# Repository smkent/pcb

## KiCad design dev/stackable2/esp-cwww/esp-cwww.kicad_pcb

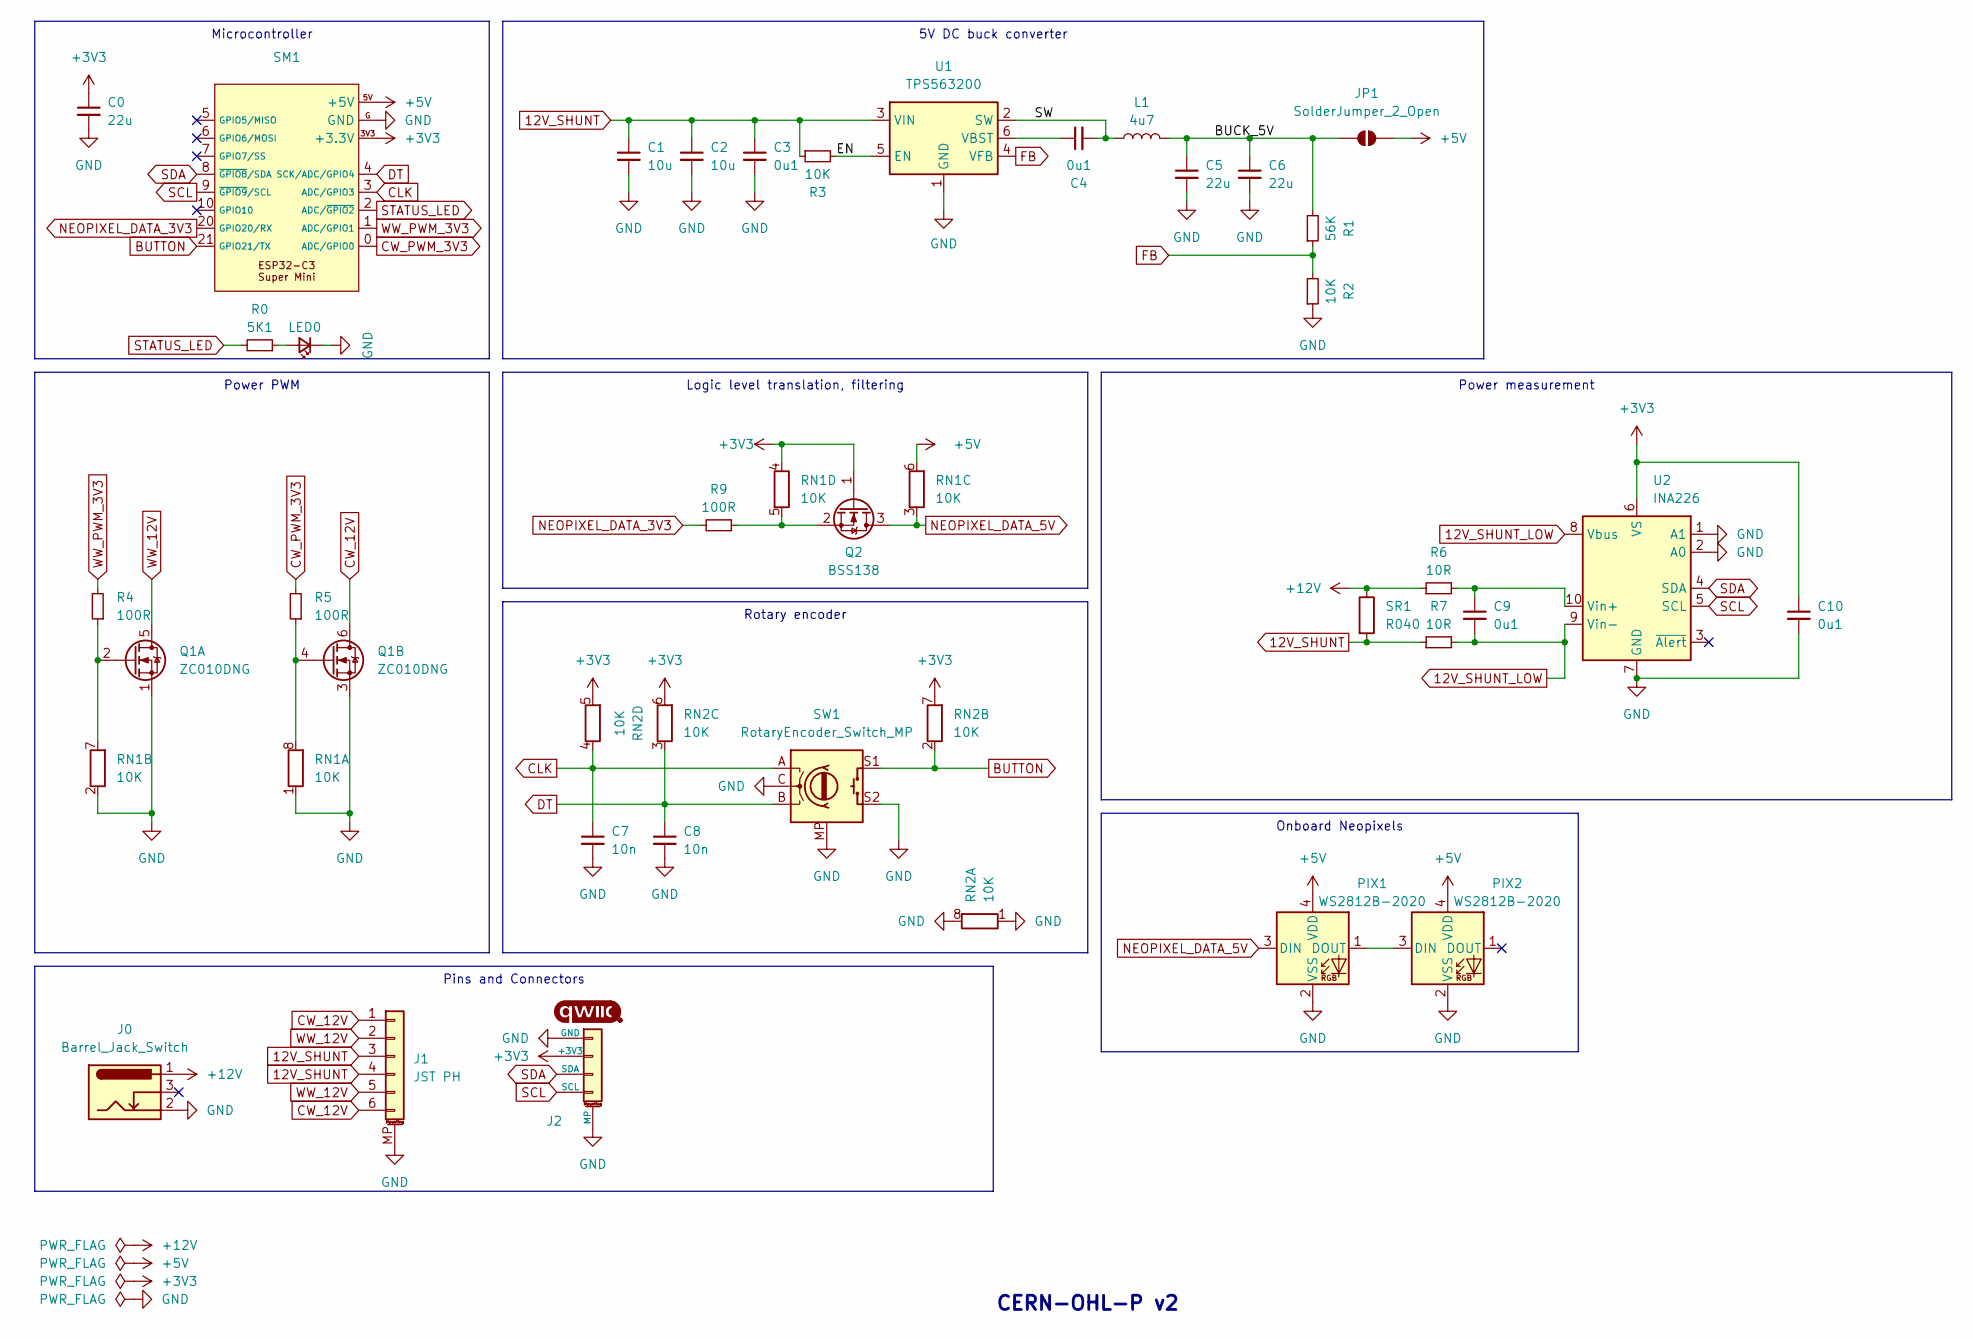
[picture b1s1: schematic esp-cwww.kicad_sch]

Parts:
C0, C5, C6: 22u; C_0603_1608Metric_Pad1.08x0.95mm_HandSolder
C1, C2: 10u; C_0603_1608Metric_Pad1.08x0.95mm_HandSolder
C3, C4: 0u1; C_0603_1608Metric_Pad1.08x0.95mm_HandSolder
C7, C8: 10n; C_0603_1608Metric_Pad1.08x0.95mm_HandSolder
C9, C10: 0u1; C_0402_1005Metric_simple; LCSC Part C1525
J0: Barrel_Jack_Switch; DC-IN_DC-050-2.0-BB_rev2
J1: JST PH; JST_PH_S6B-PH-SM4-TB_1x06-1MP_P2.00mm_Horizontal
J2: Qwiic; Qwiic-SMD-horizontal-logo
JP1: SolderJumper_2_Open; SolderJumper-2_P1.3mm_Open_TrianglePad1.0x1.5mm
L1: 4u7; IND-SMD_L2.5-W2.0_MHCHL2520
LED0: LED_Small; LED_0603_1608Metric_Pad1.05x0.95mm_HandSolder_simple
PIX1, PIX2: WS2812B-2020; LED-SK6812SIDE-A-4x1.6mm
Q1: ZC010DNG; PDFN-8_L3.2-W3.1-P0.65-LS3.4-BL-EP2; LCSC Part C36499170
Q2: BSS138; SOT-23_simple
R0: 5K1; R_0603_1608Metric_Pad0.98x0.95mm_HandSolder
R1: 56K; R_0603_1608Metric_Pad0.98x0.95mm_HandSolder
R2, R3: 10K; R_0603_1608Metric_Pad0.98x0.95mm_HandSolder
R4, R5, R9: 100R; R_0603_1608Metric_Pad0.98x0.95mm_HandSolder
R6: 10R; R_0402_1005Metric
R7: 10R; R_0402_1005Metric; LCSC Part C25077
RN1, RN2: 10K; R_Array_Convex_4x0603
SM1: ESP32-C3-Super-Mini-Castellated-SMD-only
SR1: R040; R_2512_6332Metric_Pad1.40x3.35mm_HandSolder; LCSC Part C2985725
SW1: RotaryEncoder_Switch_MP; RotaryEncoder_Alps_EC11-Switch_Combo_H20mm
U1: TPS563200; SOT-23-6_Handsoldering_simple
U2: INA226; VSSOP-10_3x3mm_P0.5mm

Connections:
12V_SHUNT: C1.1, C2.1, C3.1, J1.3, J1.4, R3.1, R7.1, SR1.2, U1.3 (VIN)
12V_SHUNT_LOW: C9.2, R7.2, U2.8 (Vbus), U2.9 (Vin-)
+3V3: C0.1, C10.1, J2.2 (+3V3), Q2.1 (G), RN1.4 (R4.1), RN2.5 (R4.2), RN2.6 (R3.2), RN2.7 (R2.2), SM1.3V3 (+3.3V), U2.6 (VS)
+5V: JP1.2 (B), PIX1.4 (VDD), PIX2.4 (VDD), RN1.6 (R3.2), SM1.5V (+5V)
+12V: J0.1, R6.1, SR1.1
/BUCK_5V: C5.1, C6.1, JP1.1 (A), L1.2, R1.2
/EN: R3.2, U1.5 (EN)
/SW: C4.2, L1.1, U1.2 (SW)
BUTTON: RN2.2 (R2.1), SM1.21 (GPIO21/TX), SW1.S1
CLK: C7.1, RN2.4 (R4.1), SM1.3 (ADC/GPIO3), SW1.A
CW_12V: J1.1, J1.6, Q1.6 (D)
CW_PWM_3V3: R5.2, SM1.0 (ADC/GPIO0)
DT: C8.1, RN2.3 (R3.1), SM1.4 (SCK/ADC/GPIO4), SW1.B
FB: R1.1, R2.2, U1.4 (VFB)
GND: C0.2, C1.2, C2.2, C3.2, C5.2, C6.2, C7.2, C8.2, C10.2, J0.2, J1.MP (MountPin), J2.1 (GND), J2.MP, LED0.1 (K), PIX1.2 (VSS), PIX2.2 (VSS), Q1.1 (S), Q1.3 (S), R2.1, RN1.1 (R1.1), RN1.2 (R2.1), RN2.1 (R1.1), RN2.8 (R1.2), SM1.G (GND), SW1.C, SW1.MP, SW1.S2, U1.1 (GND), U2.1 (A1), U2.2 (A0), U2.7 (GND)
NEOPIXEL_DATA_3V3: R9.2, SM1.20 (GPIO20/RX)
NEOPIXEL_DATA_5V: PIX1.3 (DIN), Q2.3 (D), RN1.3 (R3.1)
unnamed: LED0.2 (A), R0.1
unnamed: PIX1.1 (DOUT), PIX2.3 (DIN)
unnamed: Q1.2 (G), R4.1, RN1.7 (R2.2)
unnamed: Q1.4 (G), R5.1, RN1.8 (R1.2)
unnamed: Q2.2 (S), R9.1, RN1.5 (R4.2)
unnamed: C4.1, U1.6 (VBST)
unnamed: C9.1, R6.2, U2.10 (Vin+)
SCL: J2.4 (SCL), SM1.9 (~GPIO9/SCL), U2.5 (SCL)
SDA: J2.3 (SDA), SM1.8 (~GPIO8/SDA), U2.4 (SDA)
STATUS_LED: R0.2, SM1.2 (ADC/~GPIO2)
WW_12V: J1.2, J1.5, Q1.5 (D)
WW_PWM_3V3: R4.2, SM1.1 (ADC/GPIO1)

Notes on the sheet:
Rotary encoder
5V DC buck converter
Onboard Neopixels
Logic level translation, filtering
Power PWM
Power measurement
Pins and Connectors
Microcontroller
CERN-OHL-P v2

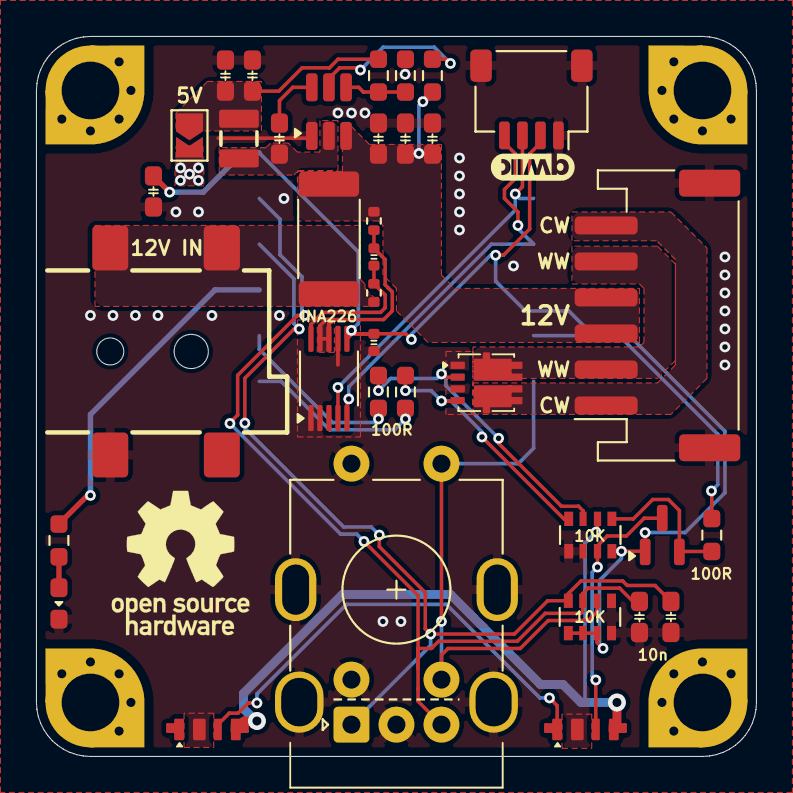
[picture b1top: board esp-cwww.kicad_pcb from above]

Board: 2 copper layers, 40.0 x 40.0 mm, 37 parts (1 on the bottom side), 29 nets.

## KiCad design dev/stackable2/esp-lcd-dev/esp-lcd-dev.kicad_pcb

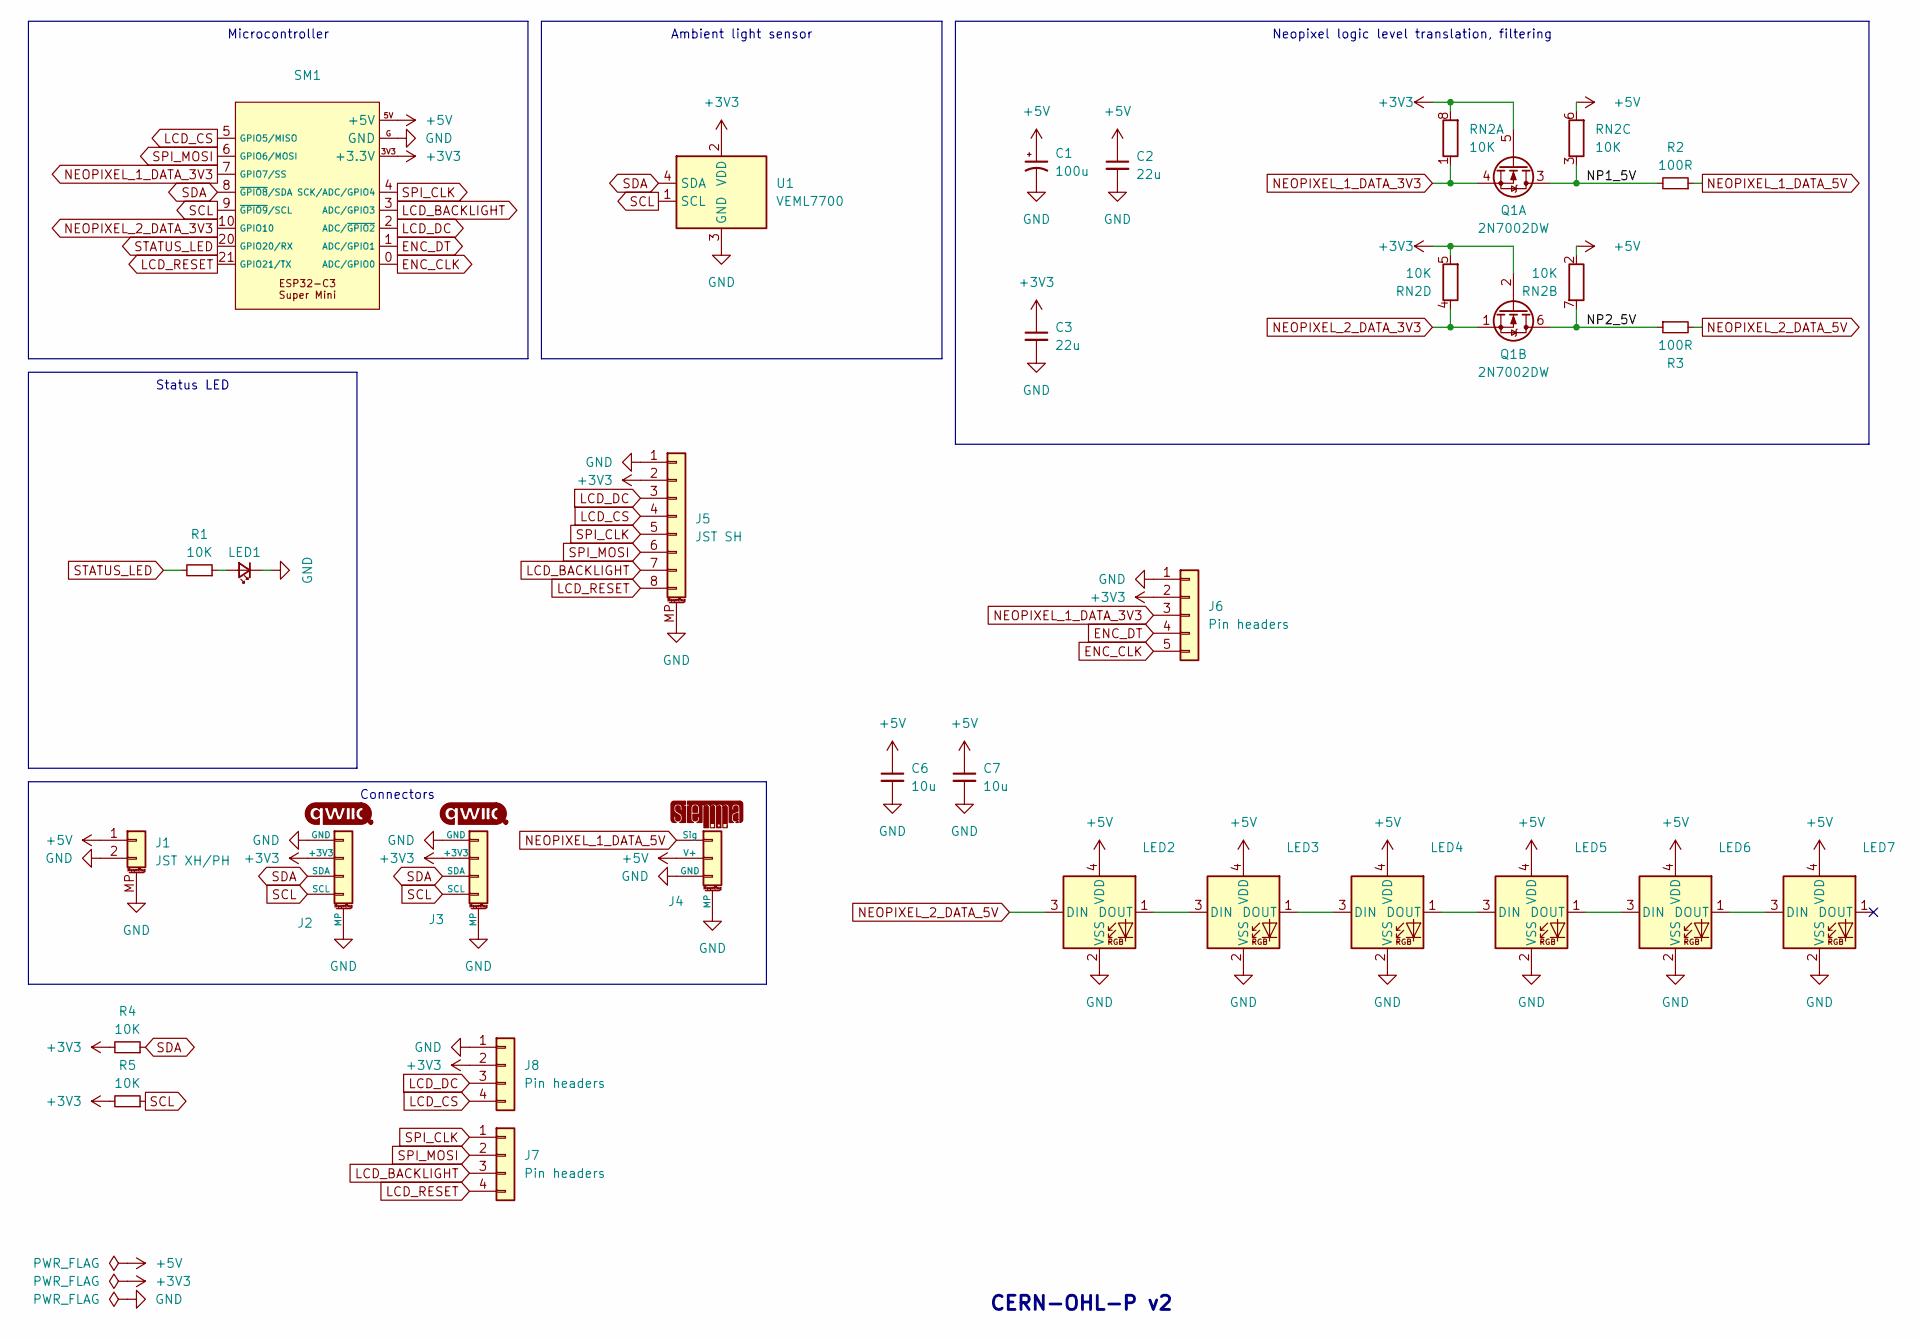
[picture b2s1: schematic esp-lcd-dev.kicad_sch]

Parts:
C1: 100u; CP_Elec_5x5.4
C2, C3: 22u; C_0603_1608Metric_Pad1.08x0.95mm_HandSolder
C6, C7: 10u; C_0603_1608Metric_Pad1.08x0.95mm_HandSolder
J1: JST XH/PH; Conn_Combo_JST-1x02-XH_PH-SMD-pad2gnd
J2, J3: Qwiic; Qwiic-SMD-horizontal-logo-bottom-pinout
J4: STEMMA-Signal; STEMMA-Signal-SMD-horizontal
J5: JST SH; JST_SH_SM08B-SRSS-TB_1x08-1MP_P1.00mm_Horizontal
J6: Pin headers; PinHeader_1x05_P2.54mm_Vertical_simple_pad1gnd
J7: Pin headers; PinSocket_1x04_P2.54mm_Vertical_SMD_Pin1Right
J8: Pin headers; PinSocket_1x04_P2.54mm_Vertical_SMD_Pin1Left
LED1: LED_Small; LED_0603_1608Metric_Pad1.05x0.95mm_HandSolder_simple
LED2, LED3, LED4, LED5, LED6, LED7: WS2812B-2020; LED-SMD_4P-L2.0-W2.0-BR-1
Q1: 2N7002DW; SOT-363_SC-70-6; LCSC Part C5190214
R1, R4, R5: 10K; R_0603_1608Metric_Pad0.98x0.95mm_HandSolder
R2, R3: 100R; R_0603_1608Metric_Pad0.98x0.95mm_HandSolder
RN2: 10K; R_Array_Convex_4x0603
SM1: ESP32-C3-Super-Mini-Castellated-SMD-only
U1: VEML7700; SENSORS-SMD_VEML7700-TR

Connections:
+3V3: C3.1, J2.2 (+3V3), J3.2 (+3V3), J5.2, J6.2, J8.2, Q1.2 (G), Q1.5 (G), R4.2, R5.2, RN2.5 (R4.2), RN2.8 (R1.2), SM1.3V3 (+3.3V), U1.2 (VDD)
+5V: C1.1, C2.1, C6.1, C7.1, J1.1, J4.2 (V+), LED2.4 (VDD), LED3.4 (VDD), LED4.4 (VDD), LED5.4 (VDD), LED6.4 (VDD), LED7.4 (VDD), RN2.2 (R2.1), RN2.6 (R3.2), SM1.5V (+5V)
/NP1_5V: Q1.3 (D), R2.2, RN2.3 (R3.1)
/NP2_5V: Q1.6 (D), R3.1, RN2.7 (R2.2)
ENC_CLK: J6.5, SM1.0 (ADC/GPIO0)
ENC_DT: J6.4, SM1.1 (ADC/GPIO1)
GND: C1.2, C2.2, C3.2, C6.2, C7.2, J1.2, J1.MP (MountPin), J2.1 (GND), J2.MP, J3.1 (GND), J3.MP, J4.3 (GND), J4.MP, J5.1, J5.MP (MountPin), J6.1, J8.1, LED1.1 (K), LED2.2 (VSS), LED3.2 (VSS), LED4.2 (VSS), LED5.2 (VSS), LED6.2 (VSS), LED7.2 (VSS), SM1.G (GND), U1.3 (GND)
LCD_BACKLIGHT: J5.7, J7.3, SM1.3 (ADC/GPIO3)
LCD_CS: J5.4, J8.4, SM1.5 (GPIO5/MISO)
LCD_DC: J5.3, J8.3, SM1.2 (ADC/~GPIO2)
LCD_RESET: J5.8, J7.4, SM1.21 (GPIO21/TX)
NEOPIXEL_1_DATA_3V3: J6.3, Q1.4 (S), RN2.1 (R1.1), SM1.7 (GPIO7/SS)
NEOPIXEL_1_DATA_5V: J4.1 (Sig), R2.1
NEOPIXEL_2_DATA_3V3: Q1.1 (S), RN2.4 (R4.1), SM1.10 (GPIO10)
NEOPIXEL_2_DATA_5V: LED2.3 (DIN), R3.2
unnamed: LED1.2 (A), R1.1
unnamed: LED2.1 (DOUT), LED3.3 (DIN)
unnamed: LED3.1 (DOUT), LED4.3 (DIN)
unnamed: LED4.1 (DOUT), LED5.3 (DIN)
unnamed: LED5.1 (DOUT), LED6.3 (DIN)
unnamed: LED6.1 (DOUT), LED7.3 (DIN)
SCL: J2.4 (SCL), J3.4 (SCL), R5.1, SM1.9 (~GPIO9/SCL), U1.1 (SCL)
SDA: J2.3 (SDA), J3.3 (SDA), R4.1, SM1.8 (~GPIO8/SDA), U1.4 (SDA)
SPI_CLK: J5.5, J7.1, SM1.4 (SCK/ADC/GPIO4)
SPI_MOSI: J5.6, J7.2, SM1.6 (GPIO6/MOSI)
STATUS_LED: R1.2, SM1.20 (GPIO20/RX)

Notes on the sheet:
Neopixel logic level translation, filtering
Connectors
Status LED
Ambient light sensor
Microcontroller
CERN-OHL-P v2

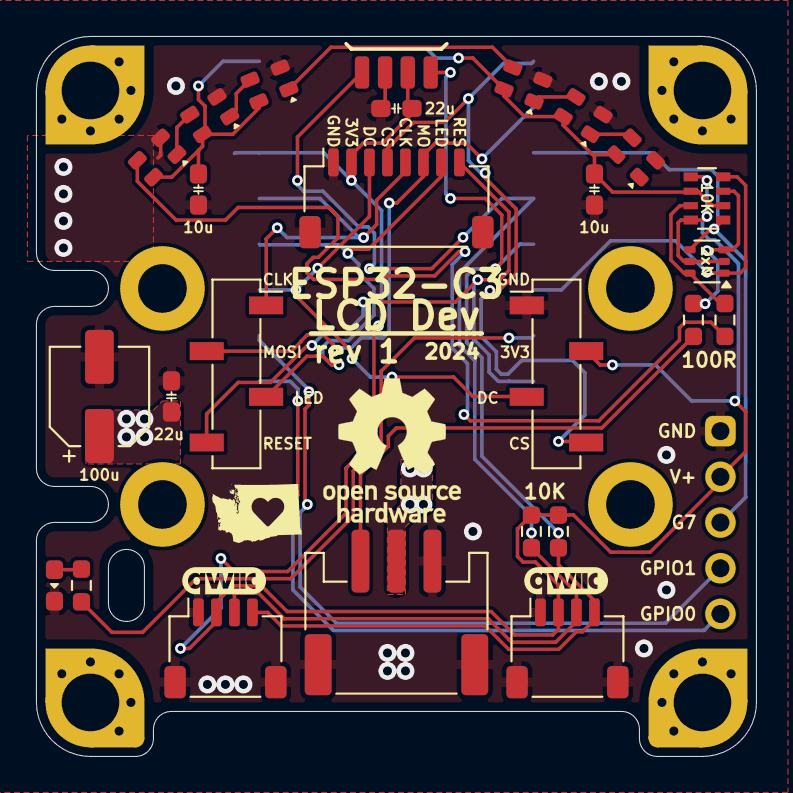
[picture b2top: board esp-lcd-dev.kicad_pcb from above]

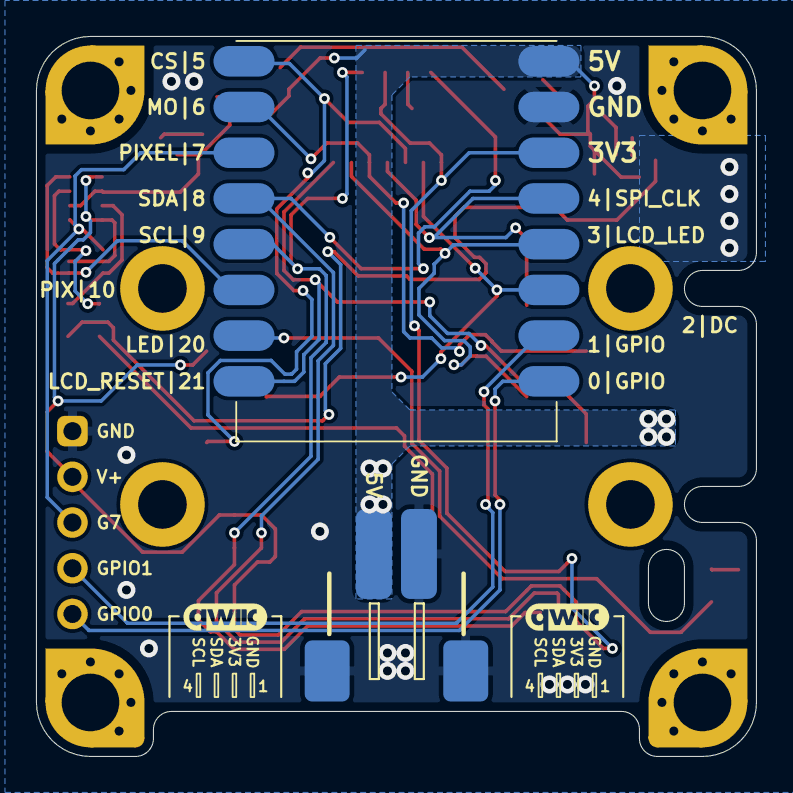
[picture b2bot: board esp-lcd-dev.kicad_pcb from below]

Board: 2 copper layers, 40.0 x 40.0 mm, 29 parts (3 on the bottom side), 26 nets.

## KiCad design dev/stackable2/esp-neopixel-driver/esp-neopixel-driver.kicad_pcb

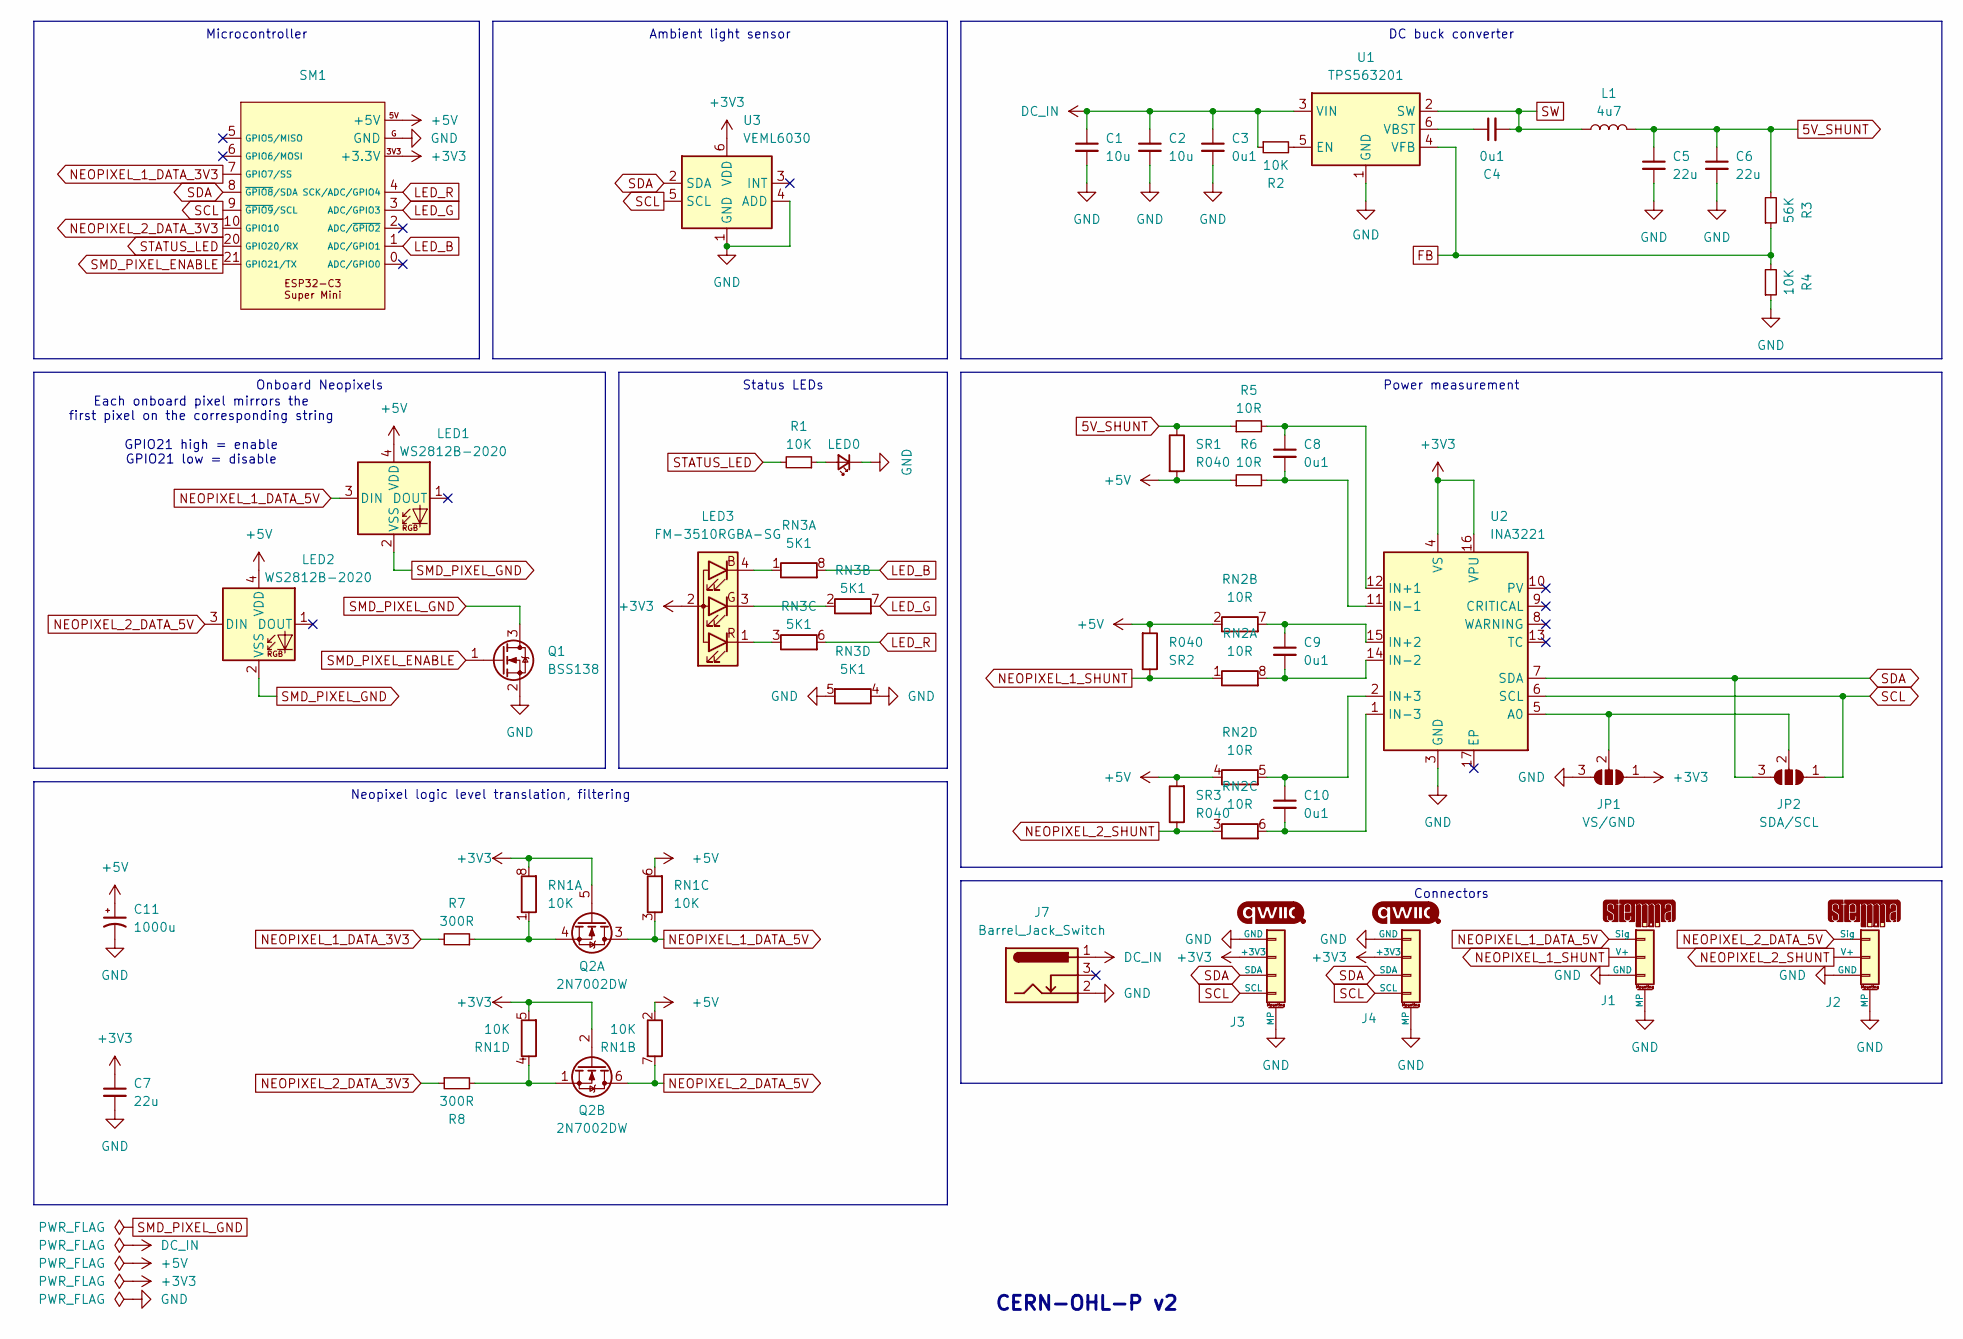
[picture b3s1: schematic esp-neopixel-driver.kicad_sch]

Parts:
C1, C2: 10u; C_0603_1608Metric_Pad1.08x0.95mm_HandSolder
C3, C4: 0u1; C_0603_1608Metric_Pad1.08x0.95mm_HandSolder
C5, C6: 22u; C_0805_2012Metric_Pad1.18x1.45mm_HandSolder
C7: 22u; C_0603_1608Metric_Pad1.08x0.95mm_HandSolder
C8, C9, C10: 0u1; C_0603_1608Metric_Pad1.08x0.95mm_HandSolder; LCSC Part C1525
C11: 1000u; CP_Elec_8x10
J1, J2: STEMMA-Signal; STEMMA-Signal-SMD-horizontal
J3, J4: Qwiic; Qwiic-SMD-horizontal-logo-bottom-pinout
J7: Barrel_Jack_Switch; DC-IN_DC-050-2.0-BB_rev2
JP1: VS/GND; SolderJumper-3_P1.0mm_Open_RoundedPad_simple
JP2: SDA/SCL; SolderJumper-3_P1.0mm_Open_RoundedPad_simple
L1: 4u7; IND-SMD_L2.5-W2.0_MHCHL2520; LCSC Part C22471106
LED0: LED_Small; LED-SMD_L1.7-W1.1-R-RD_BLUE
LED1, LED2: WS2812B-2020; LED-SMD_4P-L2.0-W2.0-BR-1
LED3: FM-3510RGBA-SG; LED-SMD_FM-3510RGBA-SG
Q1: BSS138; SOT-23_simple
Q2: 2N7002DW; SOT-363_SC-70-6; LCSC Part C5190214
R1, R2, R4: 10K; R_0603_1608Metric_Pad0.98x0.95mm_HandSolder
R3: 56K; R_0603_1608Metric_Pad0.98x0.95mm_HandSolder
R5: 10R; R_0603_1608Metric_Pad0.98x0.95mm_HandSolder_simple
R6: 10R; R_0603_1608Metric_Pad0.98x0.95mm_HandSolder_simple; LCSC Part C25077
R7, R8: 300R; R_0603_1608Metric_Pad0.98x0.95mm_HandSolder
RN1: 10K; R_Array_Convex_4x0603
RN2: 10R; R_Array_Convex_4x0603
RN3: 5K1; R_Array_Convex_4x0603
SM1: ESP32-C3-Super-Mini-Castellated-SMD-only
SR1, SR2, SR3: R040; R_2512_6332Metric_Pad1.40x3.35mm_HandSolder; LCSC Part C2985725
U1: TPS563201; SOT-23-6_Handsoldering_simple
U2: INA3221; Texas_RGV0016A_VQFN-16-1EP_4x4mm_P0.65mm_EP2.1x2.1mm_Therma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; LCSC Part C181255
U3: VEML6030; SENSORS-SMD_VEML6030

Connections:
5V_SHUNT: C5.1, C6.1, L1.2, R3.2, R5.1, SR1.1
+3V3: C7.1, J3.2 (+3V3), J4.2 (+3V3), JP1.1 (A), LED3.2 (A), Q2.2 (G), Q2.5 (G), RN1.5 (R4.2), RN1.8 (R1.2), SM1.3V3 (+3.3V), U2.4 (VS), U2.16 (VPU), U3.6 (VDD)
+5V: C11.1, LED1.4 (VDD), LED2.4 (VDD), R6.1, RN1.2 (R2.1), RN1.6 (R3.2), RN2.2 (R2.1), RN2.4 (R4.1), SM1.5V (+5V), SR1.2, SR2.2, SR3.2
DC_IN: C1.1, C2.1, C3.1, J7.1, R2.1, U1.3 (VIN)
FB: R3.1, R4.2, U1.4 (VFB)
GND: C1.2, C2.2, C3.2, C5.2, C6.2, C7.2, C11.2, J1.3 (GND), J1.MP, J2.3 (GND), J2.MP, J3.1 (GND), J3.MP, J4.1 (GND), J4.MP, J7.2, JP1.3 (B), LED0.1 (K), Q1.2 (S), R4.1, RN3.4 (R4.1), RN3.5 (R4.2), SM1.G (GND), U1.1 (GND), U2.3 (GND), U3.1 (GND), U3.4 (ADD)
LED_B: RN3.8 (R1.2), SM1.1 (ADC/GPIO1)
LED_G: RN3.7 (R2.2), SM1.3 (ADC/GPIO3)
LED_R: RN3.6 (R3.2), SM1.4 (SCK/ADC/GPIO4)
NEOPIXEL_1_DATA_3V3: R7.2, SM1.7 (GPIO7/SS)
NEOPIXEL_1_DATA_5V: J1.1 (Sig), LED1.3 (DIN), Q2.3 (D), RN1.3 (R3.1)
NEOPIXEL_1_SHUNT: J1.2 (V+), RN2.1 (R1.1), SR2.1
NEOPIXEL_2_DATA_3V3: R8.1, SM1.10 (GPIO10)
NEOPIXEL_2_DATA_5V: J2.1 (Sig), LED2.3 (DIN), Q2.6 (D), RN1.7 (R2.2)
NEOPIXEL_2_SHUNT: J2.2 (V+), RN2.3 (R3.1), SR3.1
unnamed: JP1.2 (C), JP2.2 (C), U2.5 (A0)
unnamed: LED0.2 (A), R1.1
unnamed: LED3.4 (BK), RN3.1 (R1.1)
unnamed: LED3.3 (GK), RN3.2 (R2.1)
unnamed: LED3.1 (RK), RN3.3 (R3.1)
unnamed: Q2.4 (S), R7.1, RN1.1 (R1.1)
unnamed: Q2.1 (S), R8.2, RN1.4 (R4.1)
unnamed: C9.2, RN2.8 (R1.2), U2.14 (IN-2)
unnamed: C9.1, RN2.7 (R2.2), U2.15 (IN+2)
unnamed: C10.2, RN2.6 (R3.2), U2.1 (IN-3)
unnamed: C10.1, RN2.5 (R4.2), U2.2 (IN+3)
unnamed: R2.2, U1.5 (EN)
unnamed: C4.1, U1.6 (VBST)
unnamed: C8.1, R5.2, U2.12 (IN+1)
unnamed: C8.2, R6.2, U2.11 (IN-1)
SCL: J3.4 (SCL), J4.4 (SCL), JP2.1 (A), SM1.9 (~GPIO9/SCL), U2.6 (SCL), U3.5 (SCL)
SDA: J3.3 (SDA), J4.3 (SDA), JP2.3 (B), SM1.8 (~GPIO8/SDA), U2.7 (SDA), U3.2 (SDA)
SMD_PIXEL_ENABLE: Q1.1 (G), SM1.21 (GPIO21/TX)
SMD_PIXEL_GND: LED1.2 (VSS), LED2.2 (VSS), Q1.3 (D)
STATUS_LED: R1.2, SM1.20 (GPIO20/RX)
SW: C4.2, L1.1, U1.2 (SW)

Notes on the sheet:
Onboard Neopixels
Neopixel logic level translation, filtering
Connectors
DC buck converter
Status LEDs
Microcontroller
Power measurement
Ambient light sensor
CERN-OHL-P v2
Each onboard pixel mirrors the first pixel on the corresponding string GPIO21 high = enable GPIO21 low = disable

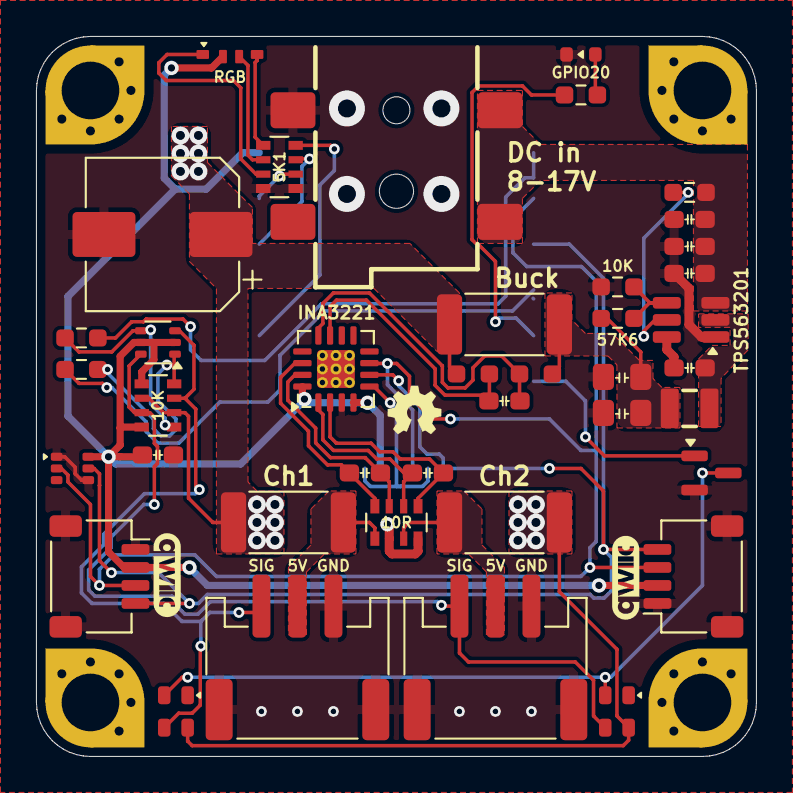
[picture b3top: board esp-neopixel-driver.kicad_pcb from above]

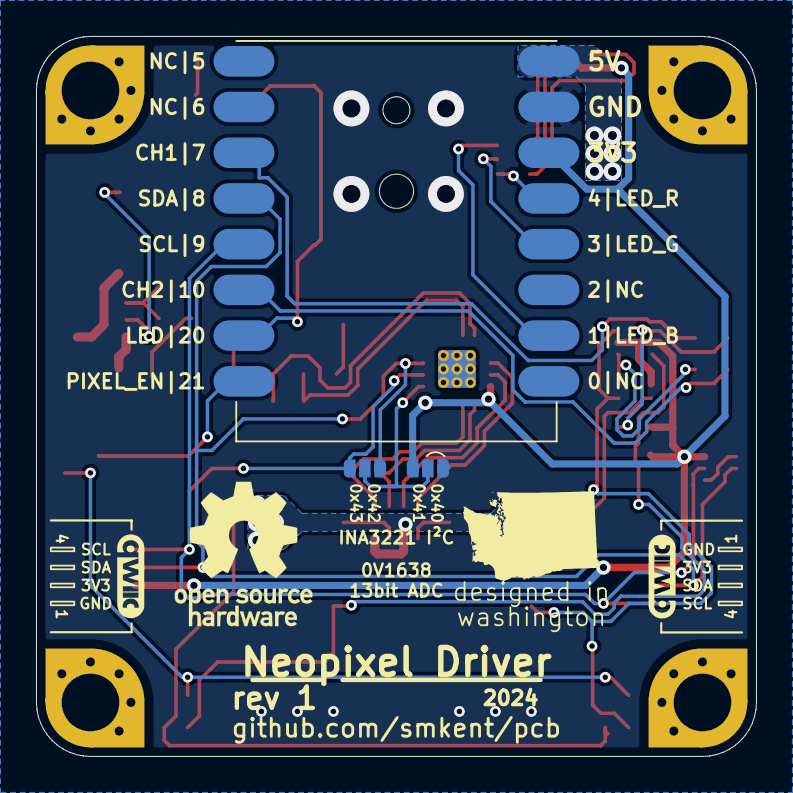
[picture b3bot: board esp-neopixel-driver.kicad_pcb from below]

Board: 2 copper layers, 40.0 x 40.0 mm, 47 parts (3 on the bottom side), 36 nets.

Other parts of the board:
MH_NE: MountingHole_3.2mm_M3_Pad_Via_corner_compact
MH_NW: MountingHole_3.2mm_M3_Pad_Via_corner_compact
MH_SE: MountingHole_3.2mm_M3_Pad_Via_corner_compact
MH_SW: MountingHole_3.2mm_M3_Pad_Via_corner_compact

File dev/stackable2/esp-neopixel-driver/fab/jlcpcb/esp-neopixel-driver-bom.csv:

Comment,Designator,Footprint,LCSC
0u1,"C8,C9,C10",custom:C_0603_1608Metric_Pad1.08x0.95mm_HandSolder,C1525
Barrel_Jack_Switch,J7,custom:DC-IN_DC-050-2.0-BB_rev2,
VEML6030,U3,lcsc:SENSORS-SMD_VEML6030,
4u7,L1,lcsc:IND-SMD_L2.5-W2.0_MHCHL2520,C22471106
Qwiic,"J3,J4",connectors:Qwiic-SMD-horizontal-logo-bottom-pinout,
LED_Small,LED0,lcsc:LED-SMD_L1.7-W1.1-R-RD_BLUE,
10K,"R1,R2,R4",Resistor_SMD:R_0603_1608Metric_Pad0.98x0.95mm_HandSolder,
FM-3510RGBA-SG,LED3,lcsc:LED-SMD_FM-3510RGBA-SG,
R040,"SR1,SR2,SR3",Resistor_SMD:R_2512_6332Metric_Pad1.40x3.35mm_HandSolder,C2985725
10u,"C1,C2",custom:C_0603_1608Metric_Pad1.08x0.95mm_HandSolder,
10K,RN1,Resistor_SMD:R_Array_Convex_4x0603,
WS2812B-2020,"LED1,LED2",lcsc:LED-SMD_4P-L2.0-W2.0-BR-1,
0u1,"C3,C4",custom:C_0603_1608Metric_Pad1.08x0.95mm_HandSolder,
300R,"R7,R8",Resistor_SMD:R_0603_1608Metric_Pad0.98x0.95mm_HandSolder,
56K,R3,Resistor_SMD:R_0603_1608Metric_Pad0.98x0.95mm_HandSolder,
INA3221,U2,custom:Texas_RGV0016A_VQFN-16-1EP_4x4mm_P0.65mm_EP2.1x2.1mm_ThermalVias,C181255
STEMMA-Signal,"J1,J2",connectors:STEMMA-Signal-SMD-horizontal,
22u,"C5,C6",custom:C_0805_2012Metric_Pad1.18x1.45mm_HandSolder,
1000u,C11,Capacitor_SMD:CP_Elec_8x10,
10R,RN2,Resistor_SMD:R_Array_Convex_4x0603,
BSS138,Q1,custom:SOT-23_simple,
10R,R6,custom:R_0603_1608Metric_Pad0.98x0.95mm_HandSolder_simple,C25077
22u,C7,custom:C_0603_1608Metric_Pad1.08x0.95mm_HandSolder,
~,SM1,modules:ESP32-C3-Super-Mini-Castellated-SMD-only,
10R,R5,custom:R_0603_1608Metric_Pad0.98x0.95mm_HandSolder_simple,
2N7002DW,Q2,Package_TO_SOT_SMD:SOT-363_SC-70-6,C5190214
TPS563201,U1,custom:SOT-23-6_Handsoldering_simple,
5K1,RN3,Resistor_SMD:R_Array_Convex_4x0603,

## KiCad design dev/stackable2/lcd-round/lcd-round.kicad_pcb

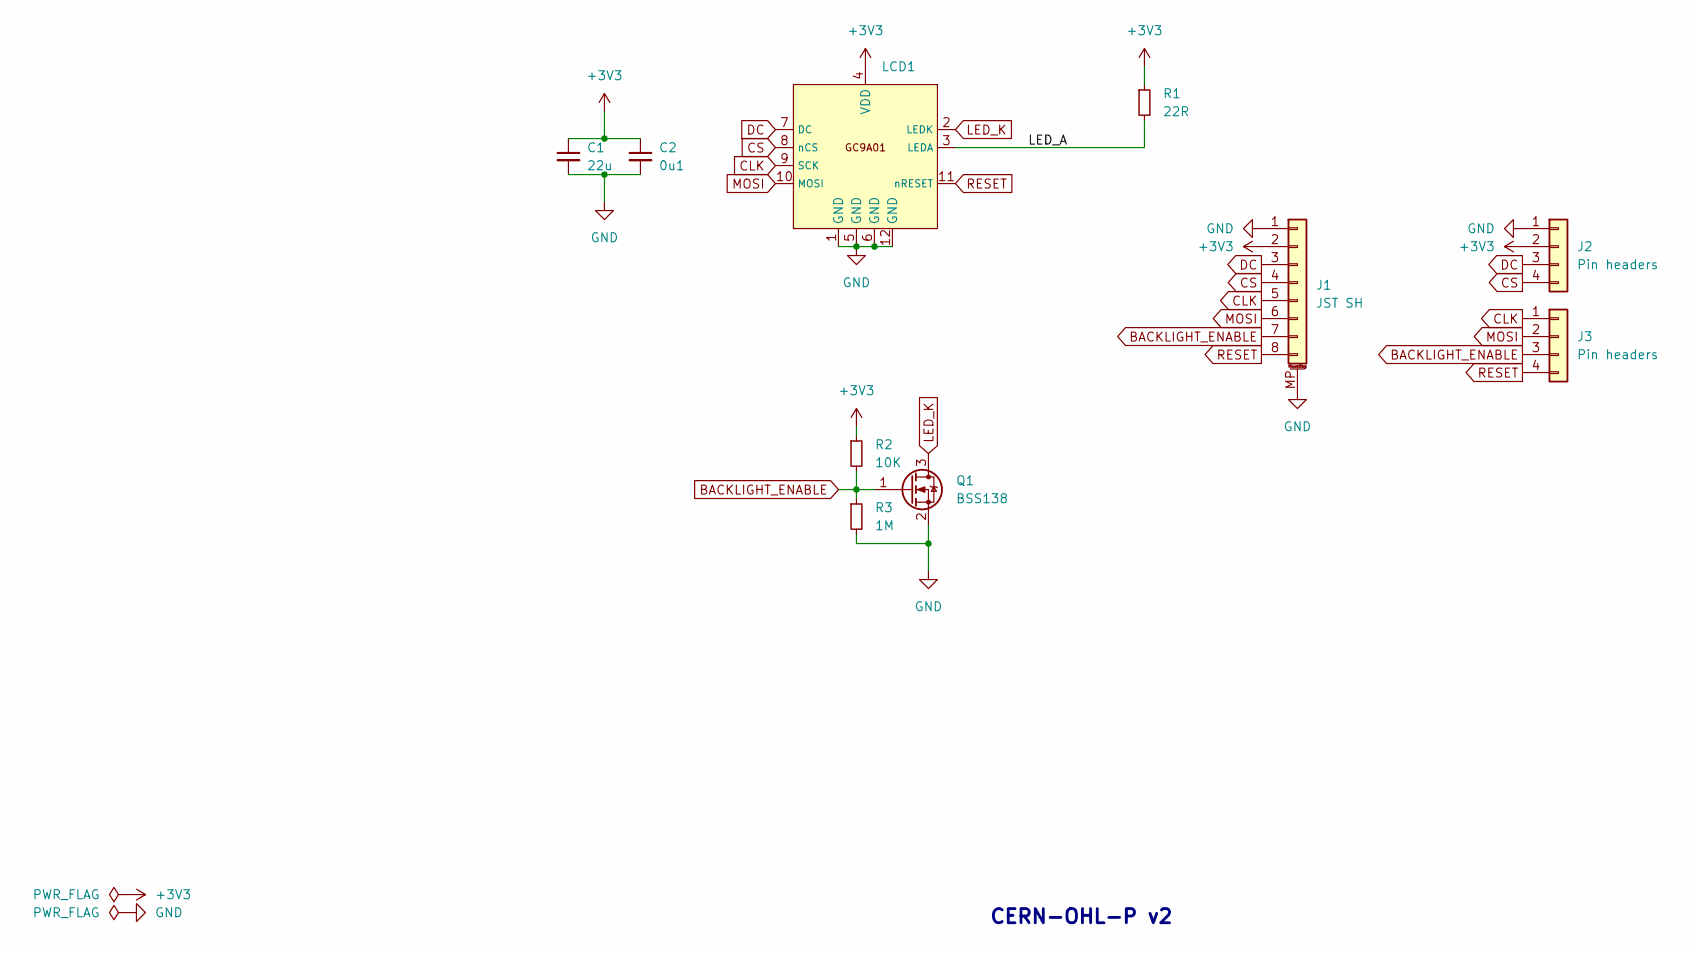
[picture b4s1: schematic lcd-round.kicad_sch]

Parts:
C1: 22u; C_0603_1608Metric_Pad1.08x0.95mm_HandSolder
C2: 0u1; C_0603_1608Metric_Pad1.08x0.95mm_HandSolder
J1: JST SH; JST_SH_SM08B-SRSS-TB_1x08-1MP_P1.00mm_Horizontal
J2: Pin headers; PinHeader_1x04_P2.54mm_Vertical_SMD_Pin1Right
J3: Pin headers; PinHeader_1x04_P2.54mm_Vertical_SMD_Pin1Left
LCD1: GC9A01; GC9A01-screen-connector-pads
Q1: BSS138; SOT-23_simple
R1: 22R; R_0603_1608Metric_Pad0.98x0.95mm_HandSolder_simple
R2: 10K; R_0603_1608Metric_Pad0.98x0.95mm_HandSolder_simple
R3: 1M; R_0603_1608Metric_Pad0.98x0.95mm_HandSolder_simple

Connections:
+3V3: C1.1, C2.1, J1.2, J2.2, LCD1.4 (VDD), R1.1, R2.1
/LED_A: LCD1.3 (LEDA), R1.2
BACKLIGHT_ENABLE: J1.7, J3.3, Q1.1 (G), R2.2, R3.1
CLK: J1.5, J3.1, LCD1.9 (SCK)
CS: J1.4, J2.4, LCD1.8 (nCS)
DC: J1.3, J2.3, LCD1.7 (DC)
GND: C1.2, C2.2, J1.1, J1.MP (MountPin), J2.1, LCD1.1 (GND), LCD1.5 (GND), LCD1.6 (GND), LCD1.12 (GND), Q1.2 (S), R3.2
LED_K: LCD1.2 (LEDK), Q1.3 (D)
MOSI: J1.6, J3.2, LCD1.10 (MOSI)
RESET: J1.8, J3.4, LCD1.11 (nRESET)

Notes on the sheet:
CERN-OHL-P v2

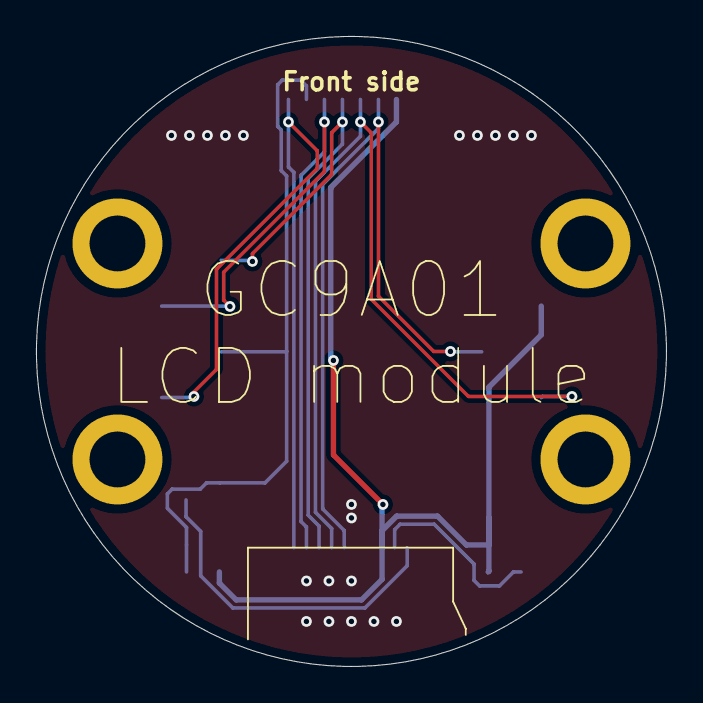
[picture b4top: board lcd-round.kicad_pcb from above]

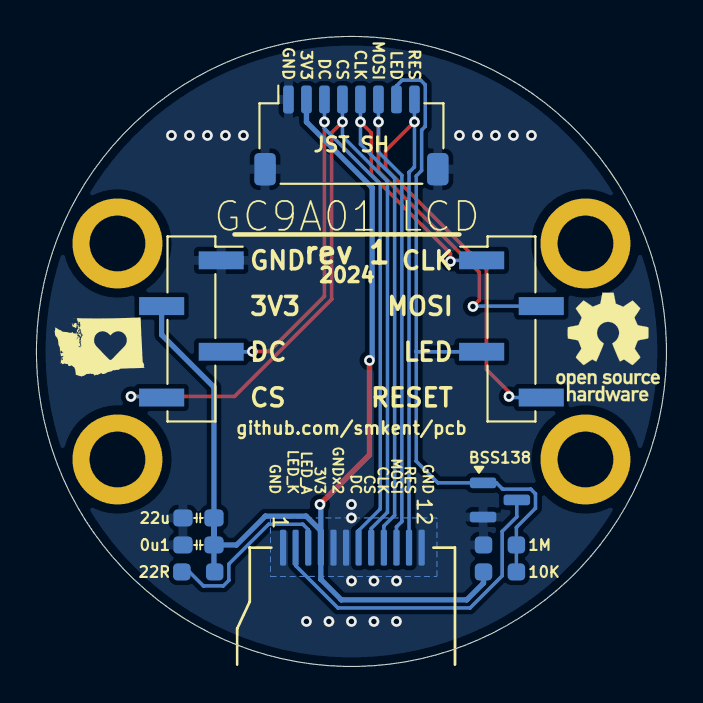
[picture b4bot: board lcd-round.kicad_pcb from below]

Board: 2 copper layers, 35.0 x 35.0 mm, 10 parts (10 on the bottom side), 10 nets.

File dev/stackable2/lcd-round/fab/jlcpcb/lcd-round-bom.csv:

Comment,Designator,Footprint,LCSC
1M,R3,custom:R_0603_1608Metric_Pad0.98x0.95mm_HandSolder_simple,
0u1,C2,custom:C_0603_1608Metric_Pad1.08x0.95mm_HandSolder,
GC9A01,LCD1,modules:GC9A01-screen-connector-pads,
22R,R1,custom:R_0603_1608Metric_Pad0.98x0.95mm_HandSolder_simple,
Pin headers,J3,Connector_PinHeader_2.54mm:PinHeader_1x04_P2.54mm_Vertical_SMD_Pin1Left,
BSS138,Q1,custom:SOT-23_simple,
JST SH,J1,connectors:JST_SH_SM08B-SRSS-TB_1x08-1MP_P1.00mm_Horizontal,
10K,R2,custom:R_0603_1608Metric_Pad0.98x0.95mm_HandSolder_simple,
Pin headers,J2,Connector_PinHeader_2.54mm:PinHeader_1x04_P2.54mm_Vertical_SMD_Pin1Right,
22u,C1,custom:C_0603_1608Metric_Pad1.08x0.95mm_HandSolder,
